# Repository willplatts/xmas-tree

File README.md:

# xmas-tree
PCB Xmas tree decoration

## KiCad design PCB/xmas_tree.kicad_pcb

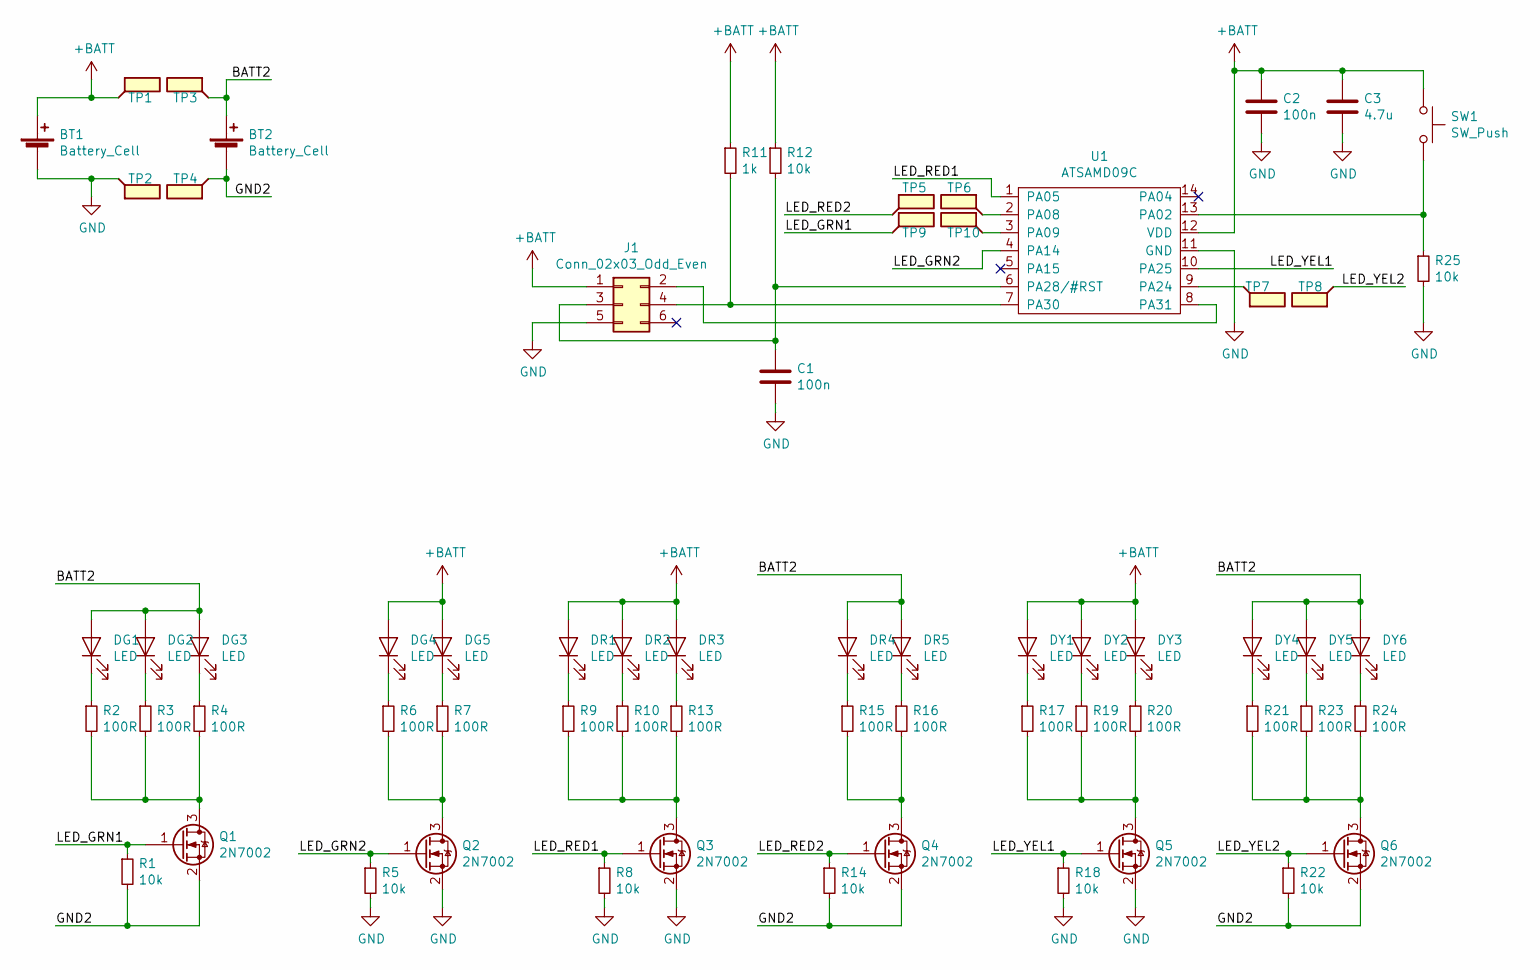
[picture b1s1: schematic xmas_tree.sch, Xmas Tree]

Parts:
BT1, BT2: Battery_Cell; BatteryHolder_MPD_BC2003_1x2032
C1, C2: 100n; C_0603_1608Metric_Pad1.05x0.95mm_HandSolder
C3: 4.7u; LED_0603_1608Metric_Pad1.05x0.95mm_HandSolder
DG1, DG2, DG3, DG4, DG5: LED; LED_0603_1608Metric_Pad1.05x0.95mm_HandSolder
DR1, DR2, DR3, DR4, DR5: LED; LED_0603_1608Metric_Pad1.05x0.95mm_HandSolder
DY1, DY2, DY3, DY4, DY5, DY6: LED; LED_0603_1608Metric_Pad1.05x0.95mm_HandSolder
J1: Conn_02x03_Odd_Even; Tag-Connect_TC2030-IDC-NL_2x03_P1.27mm_Vertical
Q1, Q2, Q3, Q4, Q5, Q6: 2N7002; SOT-23
R1, R5, R8, R12, R14, R18, R22, R25: 10k; R_0603_1608Metric_Pad1.05x0.95mm_HandSolder
R2, R3, R4, R6, R7, R9, R10, R13, R15, R16, R17, R19, R20, R21, R23, R24: 100R; R_0603_1608Metric_Pad1.05x0.95mm_HandSolder
R11: 1k; R_0603_1608Metric_Pad1.05x0.95mm_HandSolder
SW1: SW_Push; SW_SPST_B3S-1000
TP1, TP2, TP3, TP4, TP5, TP6, TP7, TP8, TP9, TP10: TestPoint_Flag; TestPoint_Pad_3.0x3.0mm
U1: ATSAMD09C; SOIC-14_3.9x8.7mm_P1.27mm

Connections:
+BATT: BT1.1 (+), C2.1, C3.1, DG4.2 (A), DG5.2 (A), DR1.2 (A), DR2.2 (A), DR3.2 (A), DY1.2 (A), DY2.2 (A), DY3.2 (A), J1.1, R11.1, R12.1, SW1.1, TP1.1, U1.12 (VDD)
/BATT2: BT2.1 (+), DG1.2 (A), DG2.2 (A), DG3.2 (A), DR4.2 (A), DR5.2 (A), DY4.2 (A), DY5.2 (A), DY6.2 (A), TP3.1
/GND2: BT2.2 (-), Q1.2 (S), Q4.2 (S), Q6.2 (S), R1.2, R14.2, R22.2, TP4.1
/LED_GRN1: Q1.1 (G), R1.1, TP9.1
/LED_GRN2: Q2.1 (G), R5.1, U1.4 (PA14)
/LED_RED1: Q3.1 (G), R8.1, U1.1 (PA05)
/LED_RED2: Q4.1 (G), R14.1, TP5.1
/LED_YEL1: Q5.1 (G), R18.1, U1.10 (PA25)
/LED_YEL2: Q6.1 (G), R22.1, TP8.1
GND: BT1.2 (-), C1.2, C2.2, C3.2, J1.5, Q2.2 (S), Q3.2 (S), Q5.2 (S), R5.2, R8.2, R18.2, R25.2, TP2.1, U1.11 (GND)
unnamed: C1.1, J1.3, R12.2, U1.6 (PA28/#RST)
unnamed: DG1.1 (K), R2.1
unnamed: DG2.1 (K), R3.1
unnamed: DG3.1 (K), R4.1
unnamed: DG4.1 (K), R6.1
unnamed: DG5.1 (K), R7.1
unnamed: DR1.1 (K), R9.1
unnamed: DR2.1 (K), R10.1
unnamed: DR3.1 (K), R13.1
unnamed: DR4.1 (K), R15.1
unnamed: DR5.1 (K), R16.1
unnamed: DY1.1 (K), R17.1
unnamed: DY2.1 (K), R19.1
unnamed: DY3.1 (K), R20.1
unnamed: DY4.1 (K), R21.1
unnamed: DY5.1 (K), R23.1
unnamed: DY6.1 (K), R24.1
unnamed: J1.2, U1.8 (PA31)
unnamed: J1.4, R11.2, U1.7 (PA30)
unnamed: Q1.3 (D), R2.2, R3.2, R4.2
unnamed: Q2.3 (D), R6.2, R7.2
unnamed: Q3.3 (D), R9.2, R10.2, R13.2
unnamed: Q4.3 (D), R15.2, R16.2
unnamed: Q5.3 (D), R17.2, R19.2, R20.2
unnamed: Q6.3 (D), R21.2, R23.2, R24.2
unnamed: R25.1, SW1.2, U1.13 (PA02)
unnamed: TP6.1, U1.2 (PA08)
unnamed: TP7.1, U1.9 (PA24)
unnamed: TP10.1, U1.3 (PA09)

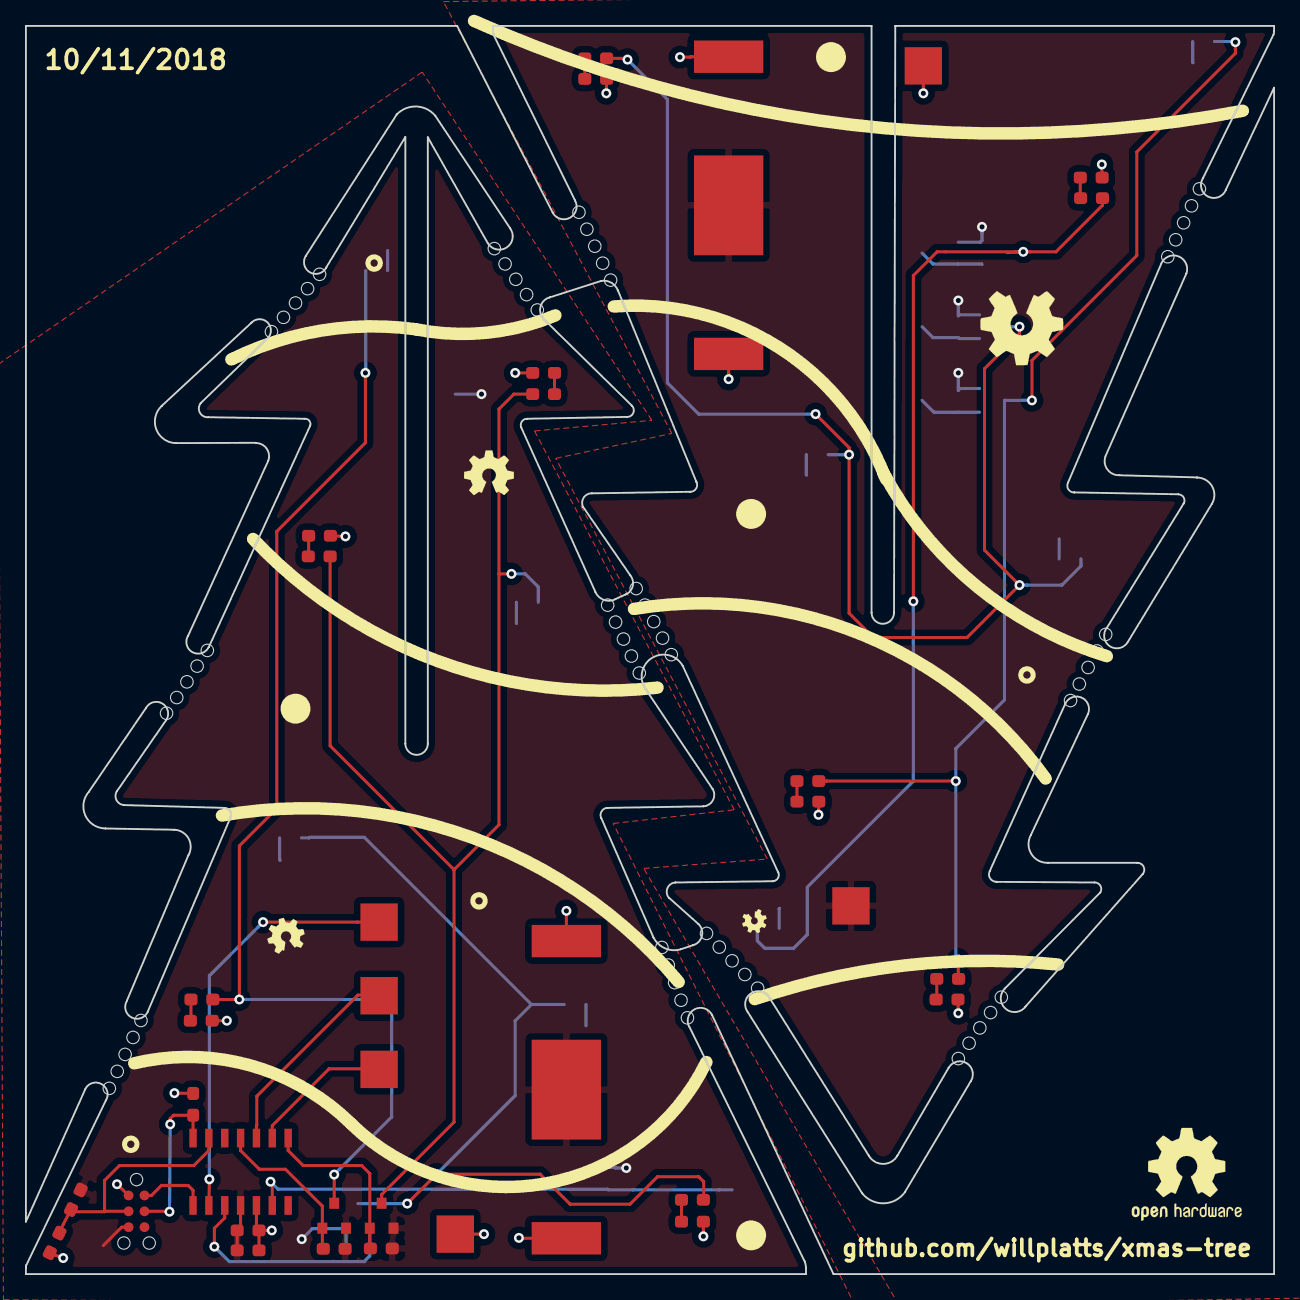
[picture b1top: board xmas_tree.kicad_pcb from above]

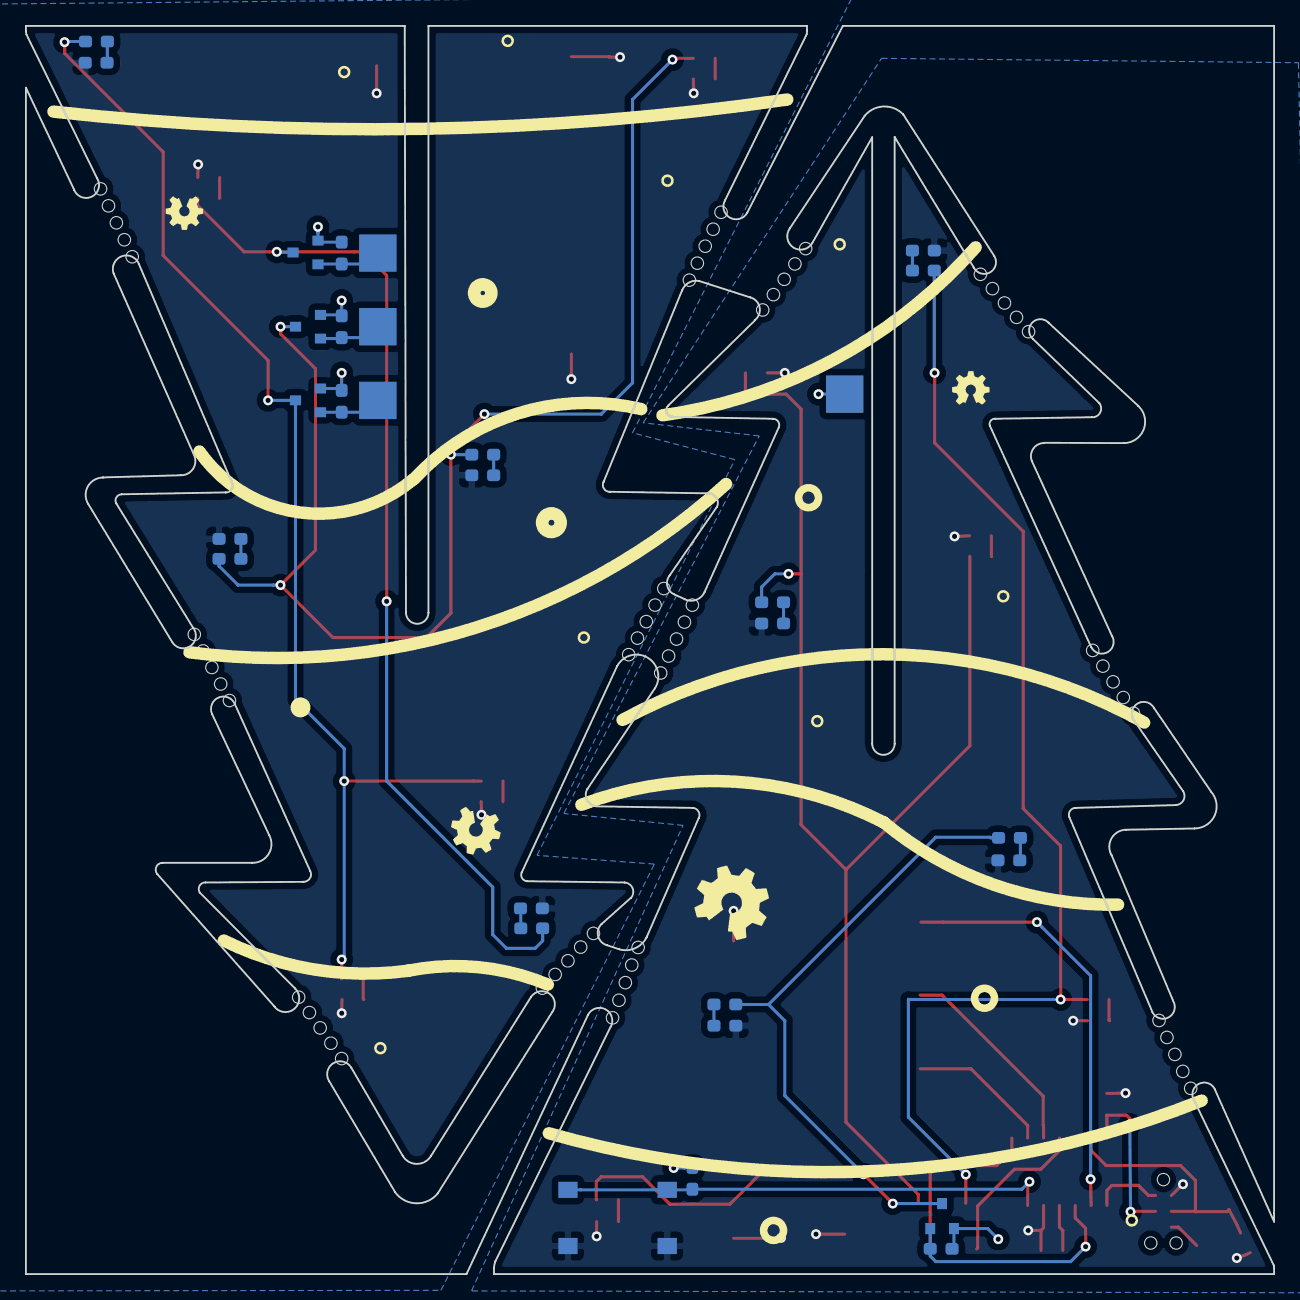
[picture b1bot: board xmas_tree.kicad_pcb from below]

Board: 2 copper layers, 100.0 x 100.0 mm, 65 parts (30 on the bottom side), 39 nets.

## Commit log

2018-11-11 Adding version 1.0 xmas tree.
2018-11-11 Adding exported PCB images
2018-11-11 Moving images to images folder
2018-11-11 Adding images to README
2018-12-20 Moving PCB files into subdirectory and adding software directory
2018-12-20 Adding initial commit of software
2018-12-20 no message
2018-12-20 Removing timer
2018-12-27 Adding latest changes to xmas tree software
